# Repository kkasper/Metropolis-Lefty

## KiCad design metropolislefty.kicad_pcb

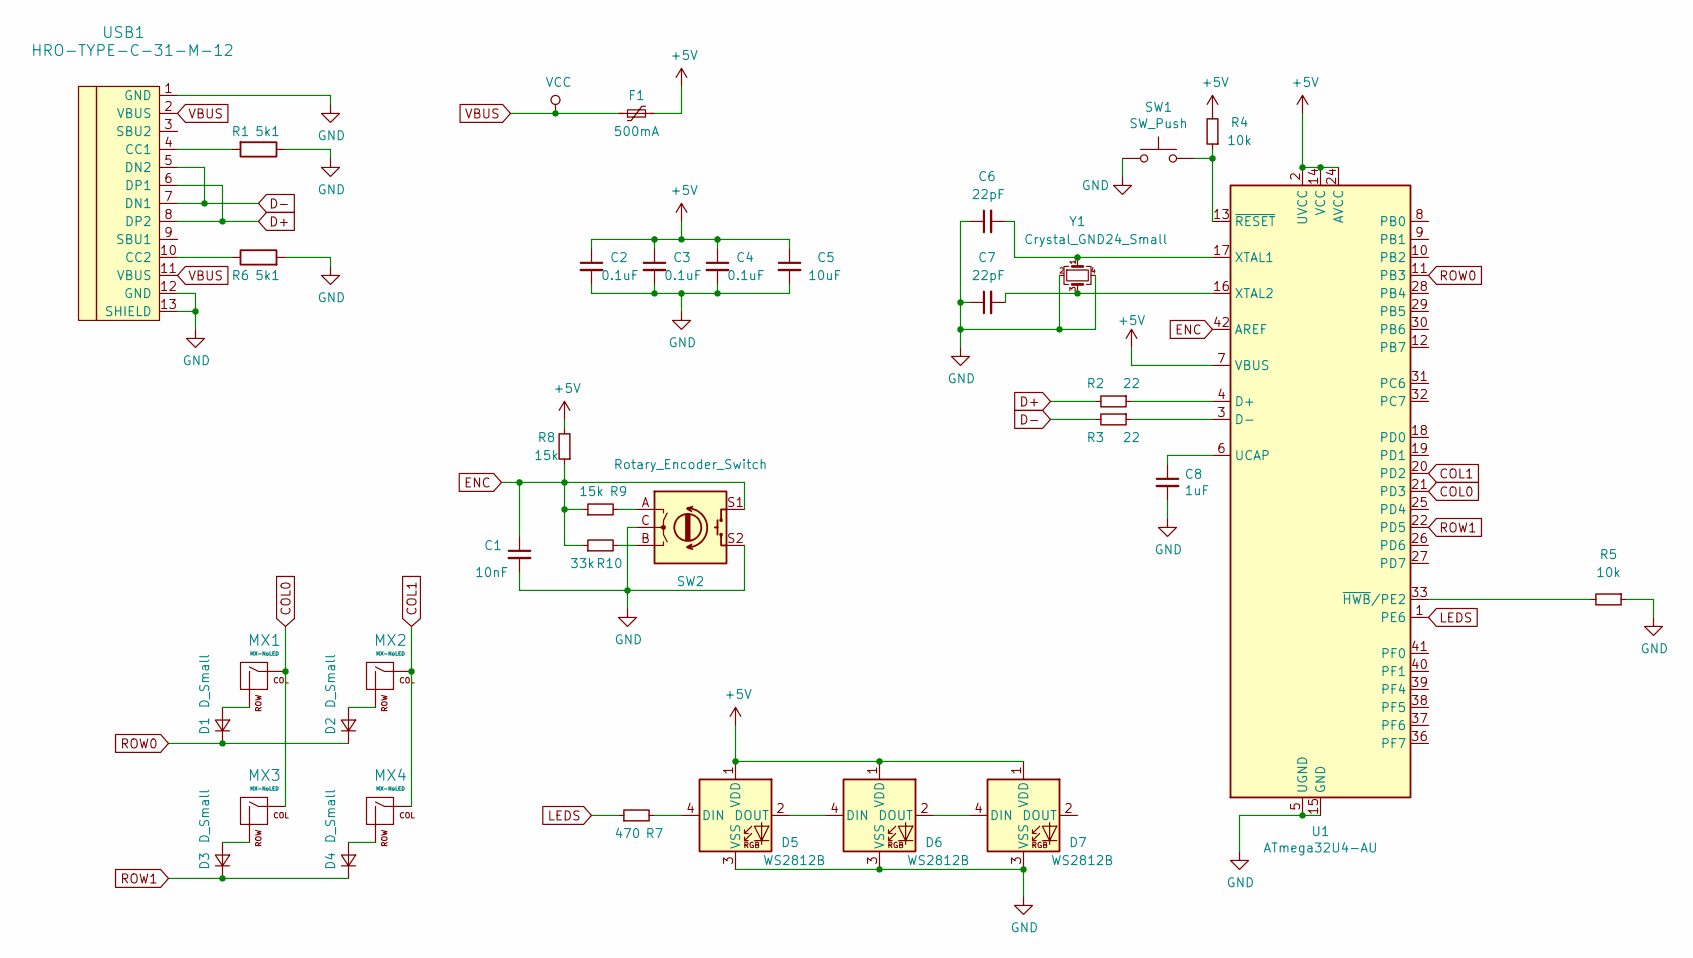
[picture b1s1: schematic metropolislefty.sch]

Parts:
C1: 10nF; C_0805_2012Metric
C2, C3, C4: 0.1uF; C_0805_2012Metric
C5: 10uF; C_0805_2012Metric
C6, C7: 22pF; C_0805_2012Metric
C8: 1uF; C_0805_2012Metric
D1, D2, D3, D4: D_Small; D_DO-35_SOD27_P7.62mm_Horizontal
D5, D6, D7: WS2812B; LED_WS2812B_PLCC4_5.0x5.0mm_P3.2mm
F1: 500mA; Fuse_1206_3216Metric
MX1, MX2, MX3, MX4: MX-NoLED; MX-1U
R1, R6: 5k1; R_0805_2012Metric
R2, R3: 22; R_0805_2012Metric
R4, R5: 10k; R_0805_2012Metric
R7: 470; R_0805_2012Metric
R8, R9: 15k; R_0805_2012Metric
R10: 33k; R_0805_2012Metric
SW1: SW_Push; SKQG-1155865
SW2: Rotary_Encoder_Switch; RotaryEncoder_Alps_EC11E-Switch_Vertical_H20mm
U1: ATmega32U4-AU; TQFP-44_10x10mm_P0.8mm
USB1: HRO-TYPE-C-31-M-12
Y1: Crystal_GND24_Small; Crystal_SMD_3225-4Pin_3.2x2.5mm

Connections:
+5V: C2.1, C3.1, C4.1, C5.1, D5.1 (VDD), D6.1 (VDD), D7.1 (VDD), F1.2, R4.2, R8.2, U1.2 (UVCC), U1.7 (VBUS), U1.14 (VCC), U1.24 (AVCC), U1.34 (VCC), U1.44 (AVCC)
COL0: MX1.1 (COL), MX3.1 (COL), U1.21 (PD3)
COL1: MX2.1 (COL), MX4.1 (COL), U1.20 (PD2)
D+: R2.2, USB1.6 (DP1), USB1.8 (DP2)
D-: R3.2, USB1.5 (DN2), USB1.7 (DN1)
ENC: C1.1, R8.1, R9.1, R10.1, SW2.S1, U1.42 (AREF)
GND: C1.2, C2.2, C3.2, C4.2, C5.2, C6.1, C7.1, C8.2, D5.3 (VSS), D6.3 (VSS), D7.3 (VSS), R1.1, R5.1, R6.2, SW1.1, SW2.C, SW2.S2, U1.5 (UGND), U1.15 (GND), U1.23 (GND), U1.35 (GND), U1.43 (GND), USB1.1 (GND), USB1.12 (GND), USB1.13 (SHIELD), Y1.2, Y1.4
LEDS: R7.1, U1.1 (PE6)
unnamed: C6.2, U1.17 (XTAL1), Y1.1
unnamed: C7.2, U1.16 (XTAL2), Y1.3
unnamed: C8.1, U1.6 (UCAP)
unnamed: D1.2 (A), MX1.2 (ROW)
unnamed: D2.2 (A), MX2.2 (ROW)
unnamed: D3.2 (A), MX3.2 (ROW)
unnamed: D4.2 (A), MX4.2 (ROW)
unnamed: D5.2 (DOUT), D6.4 (DIN)
unnamed: D5.4 (DIN), R7.2
unnamed: D6.2 (DOUT), D7.4 (DIN)
unnamed: R1.2, USB1.4 (CC1)
unnamed: R2.1, U1.4 (D+)
unnamed: R3.1, U1.3 (D-)
unnamed: R4.1, SW1.2, U1.13 (~RESET)
unnamed: R5.2, U1.33 (~HWB~/PE2)
unnamed: R6.1, USB1.10 (CC2)
unnamed: R9.2, SW2.A
unnamed: R10.2, SW2.B
ROW0: D1.1 (K), D2.1 (K), U1.11 (PB3)
ROW1: D3.1 (K), D4.1 (K), U1.22 (PD5)
VBUS: F1.1, USB1.2 (VBUS), USB1.11 (VBUS)

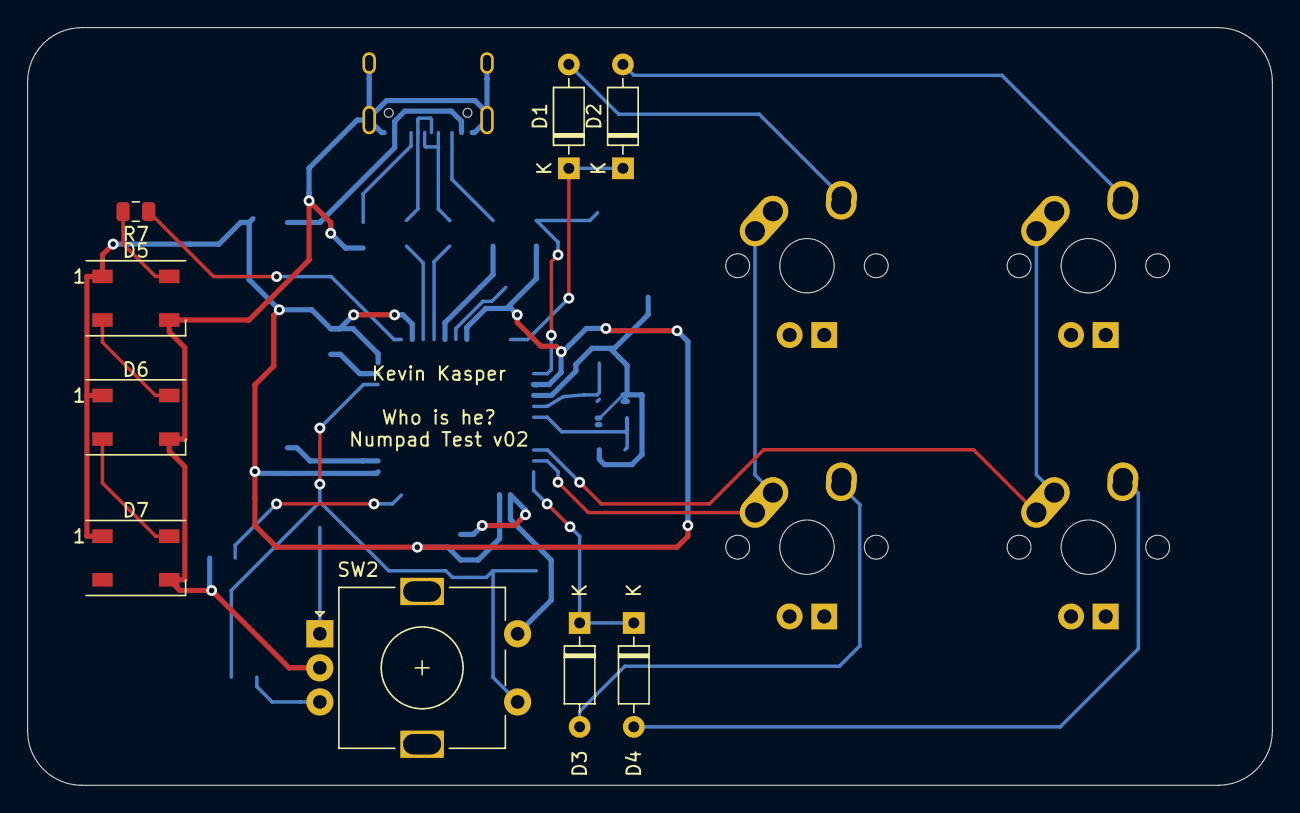
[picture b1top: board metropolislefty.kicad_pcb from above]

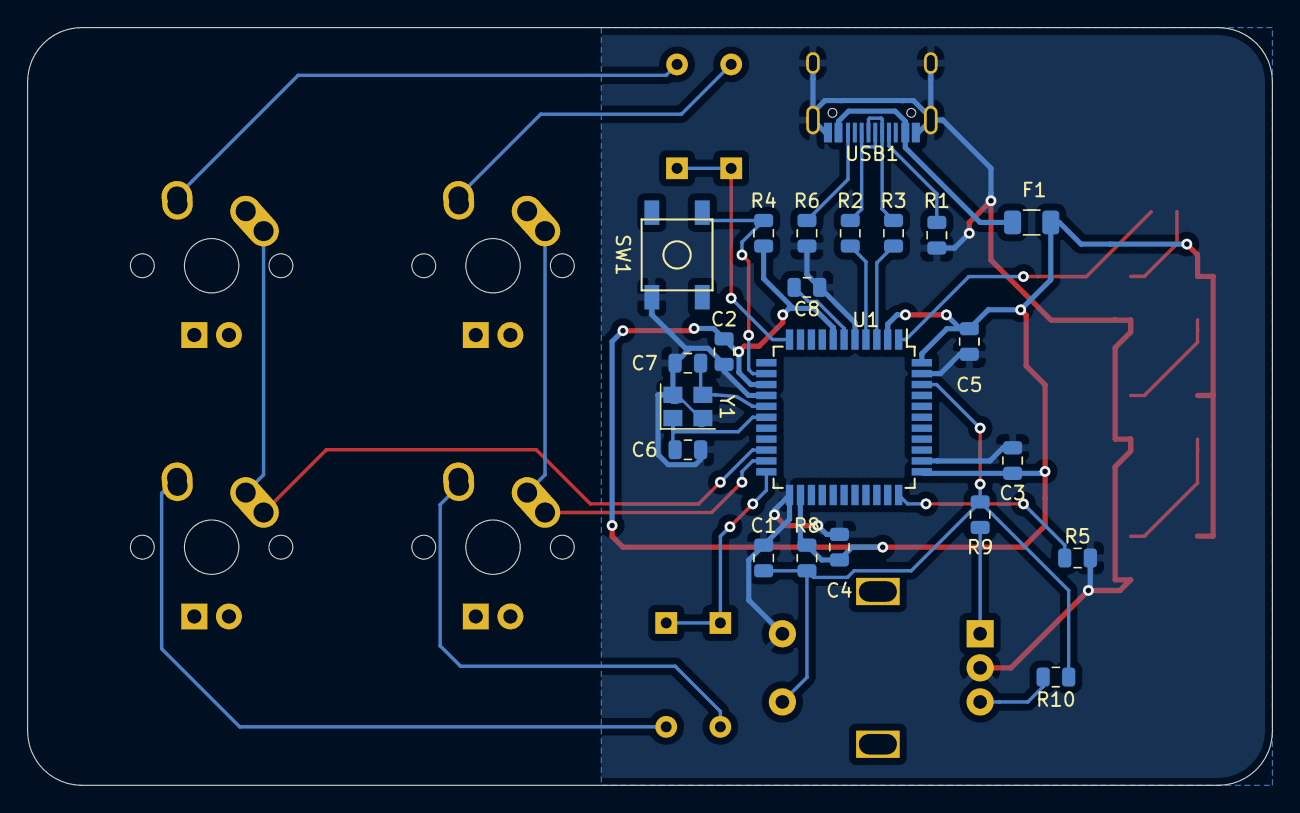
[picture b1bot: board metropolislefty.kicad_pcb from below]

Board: 2 copper layers, 91.3 x 55.6 mm, 35 parts (22 on the bottom side), 29 nets.

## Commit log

2019-12-10 Initial commit.
2019-12-10 Added minimal MCU
2019-12-11 Created test board.
2020-02-01 Alpha v0.0.1 Rev 0
2020-02-13 Created version 1.0 for fabrication
2020-05-15 Revision 1 Test w/ USB C
